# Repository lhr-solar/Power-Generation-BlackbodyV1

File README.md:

# Power Generation Blackbody
Gathers irradiance and temperature data for telemetry and MPPT algorithmic input.

**Blackbody**

Gathers irradiance reading from sensor board and temperature reading from thermocouple. Sends data on telemetry CAN bus.

**Irradiance Sensor Board**

Holds the irradiance sensor. Placed on the top shell between solar modules and connected with wires to blackbody

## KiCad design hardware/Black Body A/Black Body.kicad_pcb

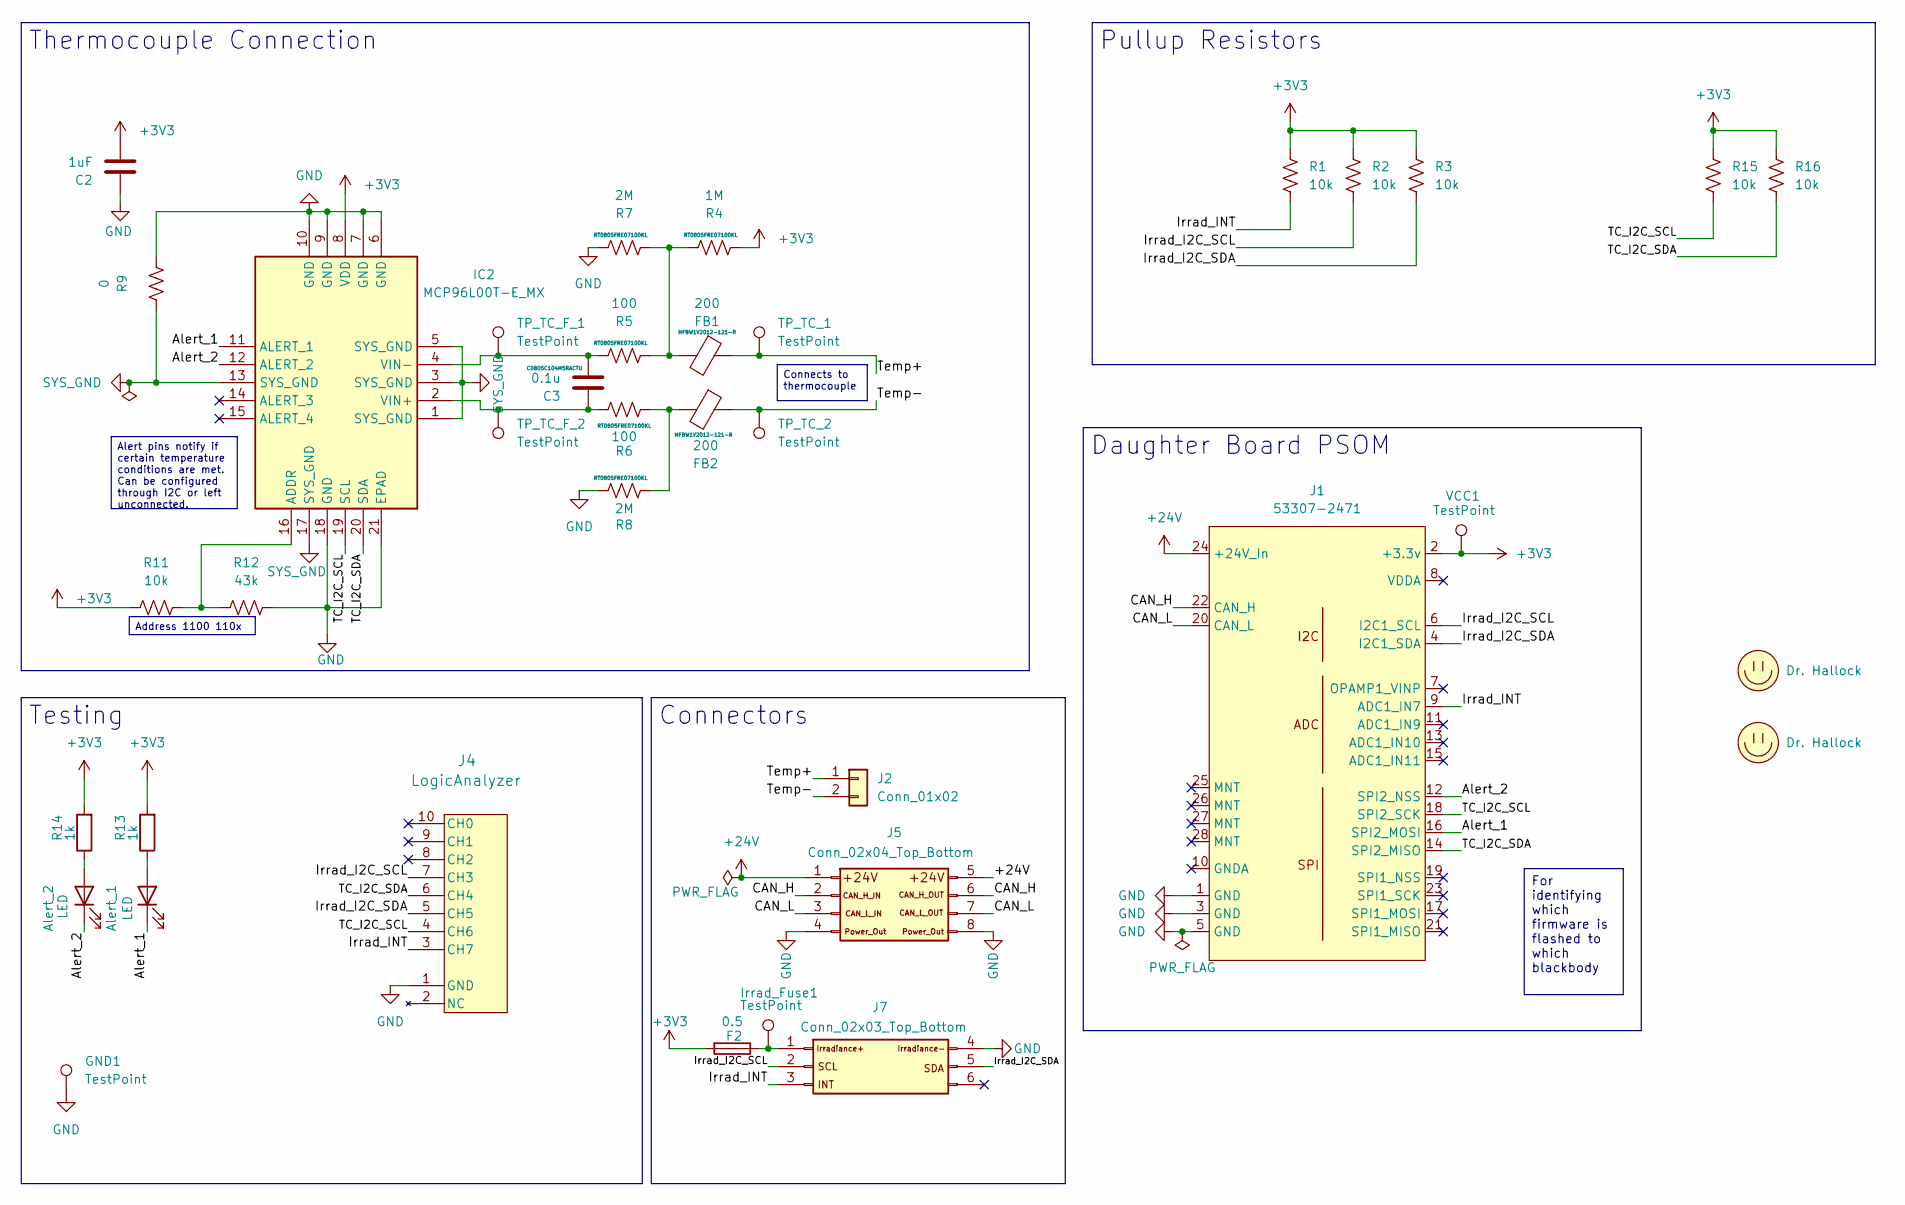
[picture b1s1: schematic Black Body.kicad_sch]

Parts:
Alert_1, Alert_2: LED; LED_0603_1608Metric_Pad1.05x0.95mm_HandSolder
C2: 1uF; C_0805_2012Metric_Pad1.18x1.45mm_HandSolder
C3: 0.1u; C_0805_2012Metric_Pad1.18x1.45mm_HandSolder
F2: 0.5; Fuseholder_Blade_Mini_Keystone_3568
FB1, FB2: 200; L_0603_1608Metric_Pad1.05x0.95mm_HandSolder
GND1: TestPoint; TestPoint_Keystone_5005-5009_Compact
IC2: MCP96L00T-E_MX; QFN65P500X500X100-21N-D; Manufacturer_Part_Number MCP96L00T-E/MX; Mouser Part Number 579-MCP96L00T-E/MX
Irrad_Fuse1: TestPoint; TestPoint_Keystone_5005-5009_Compact
J1: 53307-2471; PeripheralSOM
J2: Conn_01x02; 105313-2102
J4: LogicAnalyzer; CONN_SFH11-xxxC-D05-ST-XX_SUL; Digikey P/N S9194-ND
J5: Conn_02x04_Top_Bottom; Molex_Nano-Fit_105314-xx08_2x04_P2.50mm_Horizontal
J7: Conn_02x03_Top_Bottom; 105314-1306
LOGO1: Dr. Hallock; LHRs_LOGO
LOGO2: Dr. Hallock; Hallock_Image_Tiny
R1, R2, R3, R11, R15, R16: 10k; R_0603_1608Metric_Pad0.98x0.95mm_HandSolder
R4: 1M; R_0603_1608Metric_Pad0.98x0.95mm_HandSolder
R5, R6: 100; R_0603_1608Metric_Pad0.98x0.95mm_HandSolder
R7, R8: 2M; R_0603_1608Metric_Pad0.98x0.95mm_HandSolder
R9: 0; R_0603_1608Metric_Pad0.98x0.95mm_HandSolder
R12: 43k; R_0603_1608Metric_Pad0.98x0.95mm_HandSolder
R13, R14: 1k; R_0603_1608Metric_Pad0.98x0.95mm_HandSolder
TP_TC_1, TP_TC_2: TestPoint; TestPoint_Keystone_5005-5009_Compact
TP_TC_F_1, TP_TC_F_2: TestPoint; TestPoint_Keystone_5005-5009_Compact
VCC1: TestPoint; TestPoint_Keystone_5005-5009_Compact

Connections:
+3V3: C2.2, F2.2, IC2.8 (VDD), J1.2 (+3.3v), R1.1, R2.1, R3.1, R4.2, R11.2, R13.2, R14.2, R15.1, R16.1, VCC1.1
+24V: J1.24 (+24V_In), J5.1, J5.5
/Alert_1: Alert_1.1 (K), IC2.11 (ALERT_1), J1.16 (SPI2_MOSI)
/Alert_2: Alert_2.1 (K), IC2.12 (ALERT_2), J1.12 (SPI2_NSS)
/CAN_H: J1.22 (CAN_H), J5.2, J5.6
/CAN_L: J1.20 (CAN_L), J5.3, J5.7
/Irrad_I2C_SCL: J1.6 (I2C1_SCL), J4.7 (CH3), J7.2, R2.2
/Irrad_I2C_SDA: J1.4 (I2C1_SDA), J4.5 (CH5), J7.5, R3.2
/Irrad_INT: J1.9 (ADC1_IN7), J4.3 (CH7), J7.3, R1.2
/TC_I2C_SCL: IC2.19 (SCL), J1.18 (SPI2_SCK), J4.4 (CH6), R15.2
/TC_I2C_SDA: IC2.20 (SDA), J1.14 (SPI2_MISO), J4.6 (CH4), R16.2
/Temp+: FB1.1, J2.1, TP_TC_1.1
/Temp-: FB2.1, J2.2, TP_TC_2.1
GND: C2.1, GND1.1, IC2.6 (GND), IC2.7 (GND), IC2.9 (GND), IC2.10 (GND), IC2.18 (GND), IC2.21 (EPAD), J1.1 (GND), J1.3 (GND), J1.5 (GND), J4.1 (GND), J5.4, J5.8, J7.4, R7.1, R8.1, R9.2, R12.1
unnamed: Alert_1.2 (A), R13.1
unnamed: Alert_2.2 (A), R14.1
unnamed: FB1.2, R4.1, R5.2, R7.2
unnamed: FB2.2, R6.2, R8.2
unnamed: IC2.16 (ADDR), R11.1, R12.2
unnamed: C3.1, IC2.2 (VIN+), R6.1, TP_TC_F_2.1
unnamed: C3.2, IC2.4 (VIN-), R5.1, TP_TC_F_1.1
unnamed: F2.1, Irrad_Fuse1.1, J7.1
SYS_GND: IC2.1 (SYS_GND), IC2.3 (SYS_GND), IC2.5 (SYS_GND), IC2.13 (SYS_GND), IC2.17 (SYS_GND), R9.1

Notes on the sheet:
Connects to thermocouple
Daughter Board PSOM
Pullup Resistors
Address 1100 110x
For identifying which firmware is flashed to which blackbody
Thermocouple Connection
Testing
Alert pins notify if certain temperature conditions are met. Can be configured through I2C or left unconnected.
Connectors

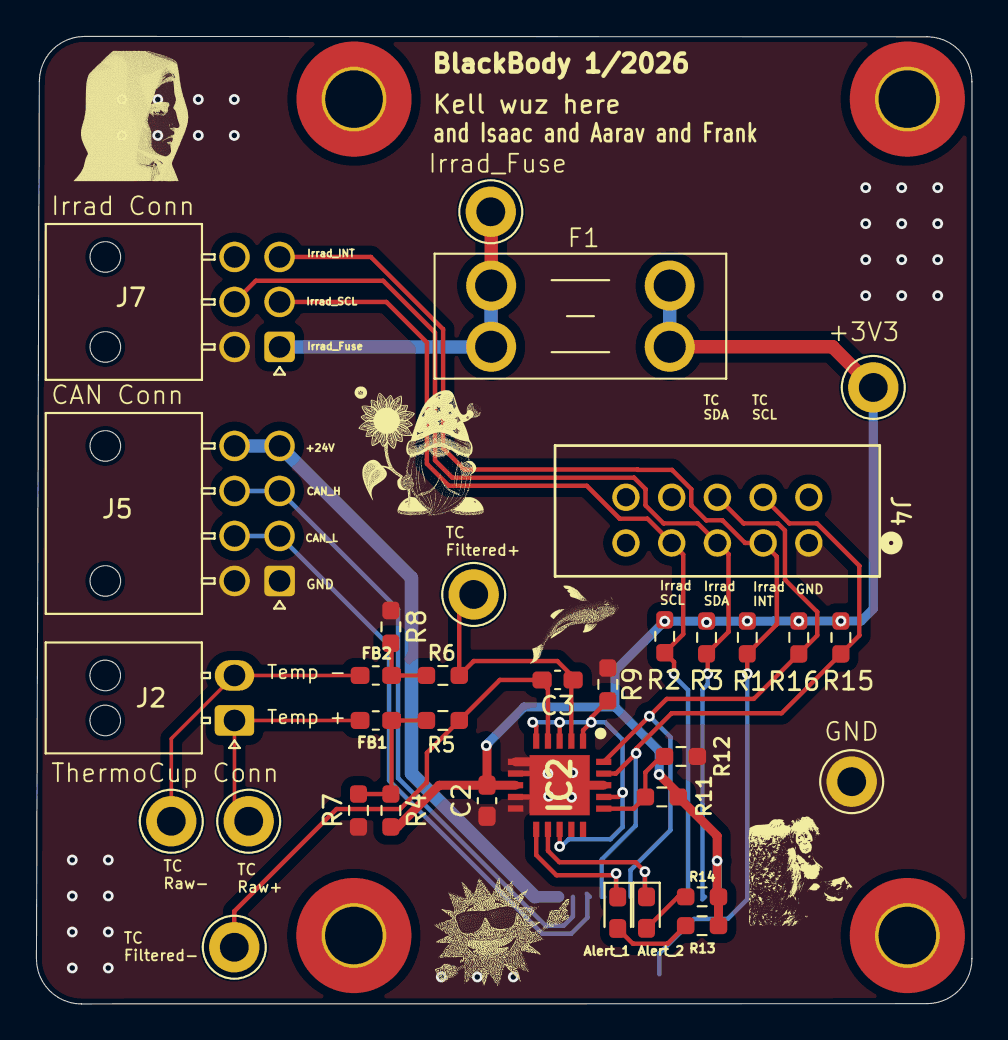
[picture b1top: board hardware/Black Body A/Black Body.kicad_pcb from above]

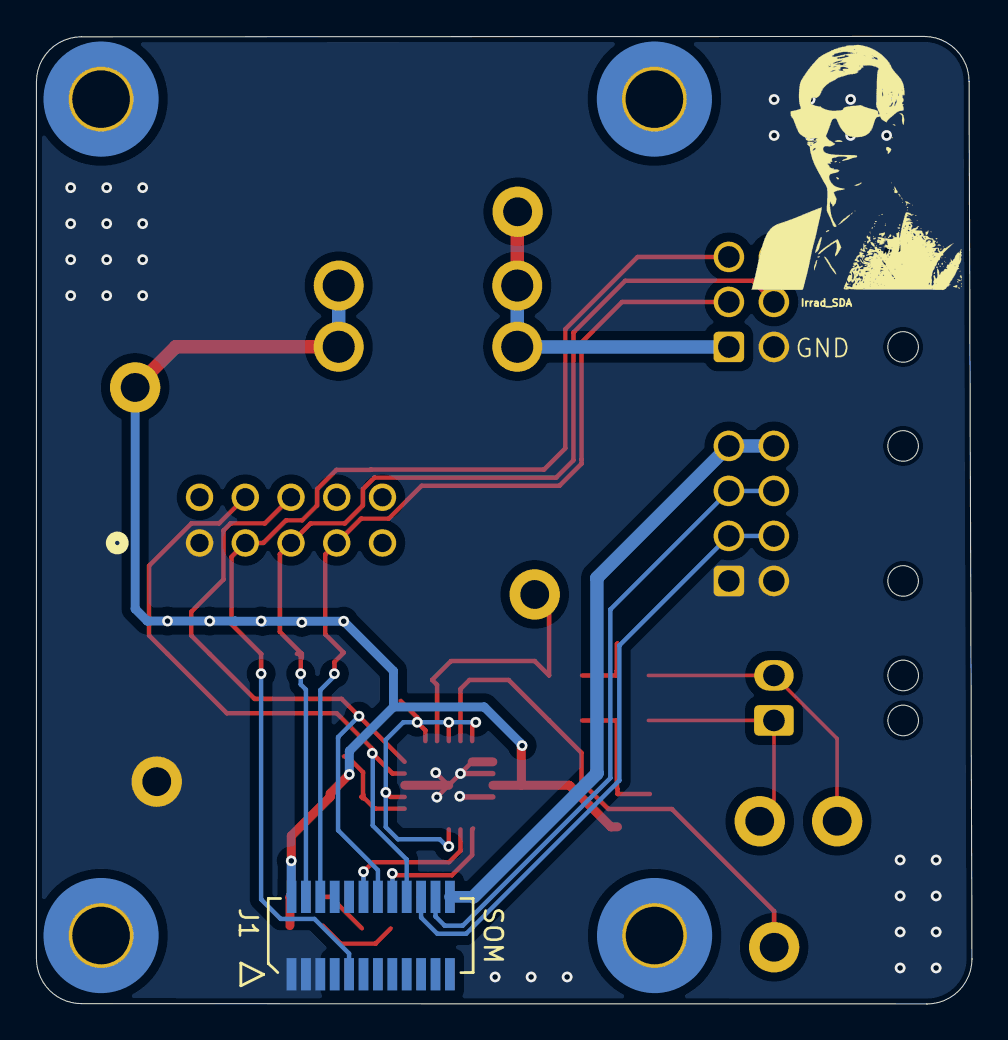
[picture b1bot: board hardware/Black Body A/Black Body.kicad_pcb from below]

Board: 2 copper layers, 52.0 x 53.8 mm, 37 parts (2 on the bottom side), 23 nets.

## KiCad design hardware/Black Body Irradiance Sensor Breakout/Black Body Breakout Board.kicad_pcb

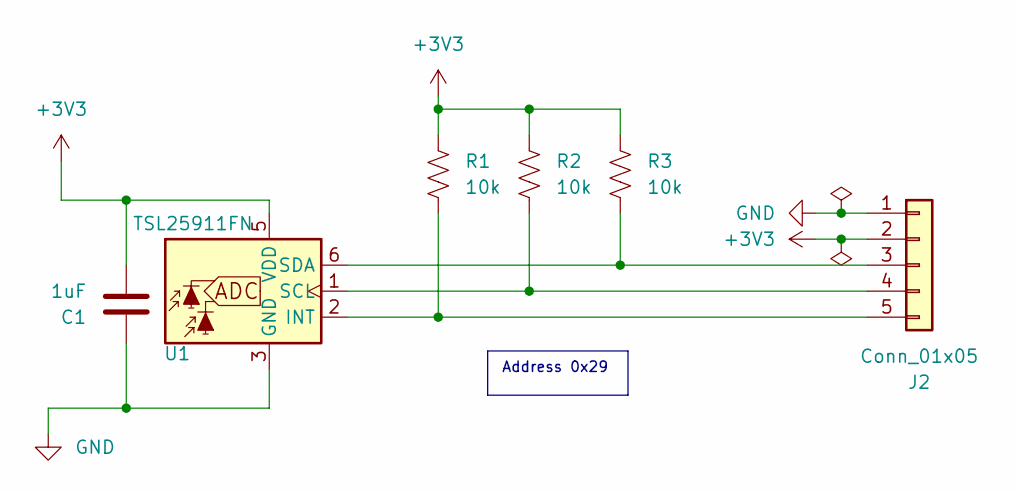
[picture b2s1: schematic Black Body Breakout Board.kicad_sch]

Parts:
C1: 1uF; C_0201_0603Metric_Pad0.64x0.40mm_HandSolder
J2: Conn_01x05; Molex_Nano-Fit_105313-xx05_1x05_P2.50mm_Horizontal
R1, R2, R3: 10k; R_0805_2012Metric
U1: TSL25911FN; AMS_TSL25911FN

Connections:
+3V3: C1.2, J2.2, R1.1, R2.1, R3.1, U1.5 (VDD)
GND: C1.1, J2.1, U1.3 (GND)
unnamed: J2.3, R3.2, U1.6 (SDA)
unnamed: J2.4, R2.2, U1.1 (SCL)
unnamed: J2.5, R1.2, U1.2 (INT)

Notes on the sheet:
Address 0x29

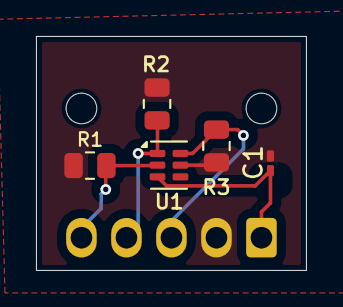
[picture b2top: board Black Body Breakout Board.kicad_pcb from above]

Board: 2 copper layers, 15.0 x 13.0 mm, 6 parts (1 on the bottom side), 5 nets.

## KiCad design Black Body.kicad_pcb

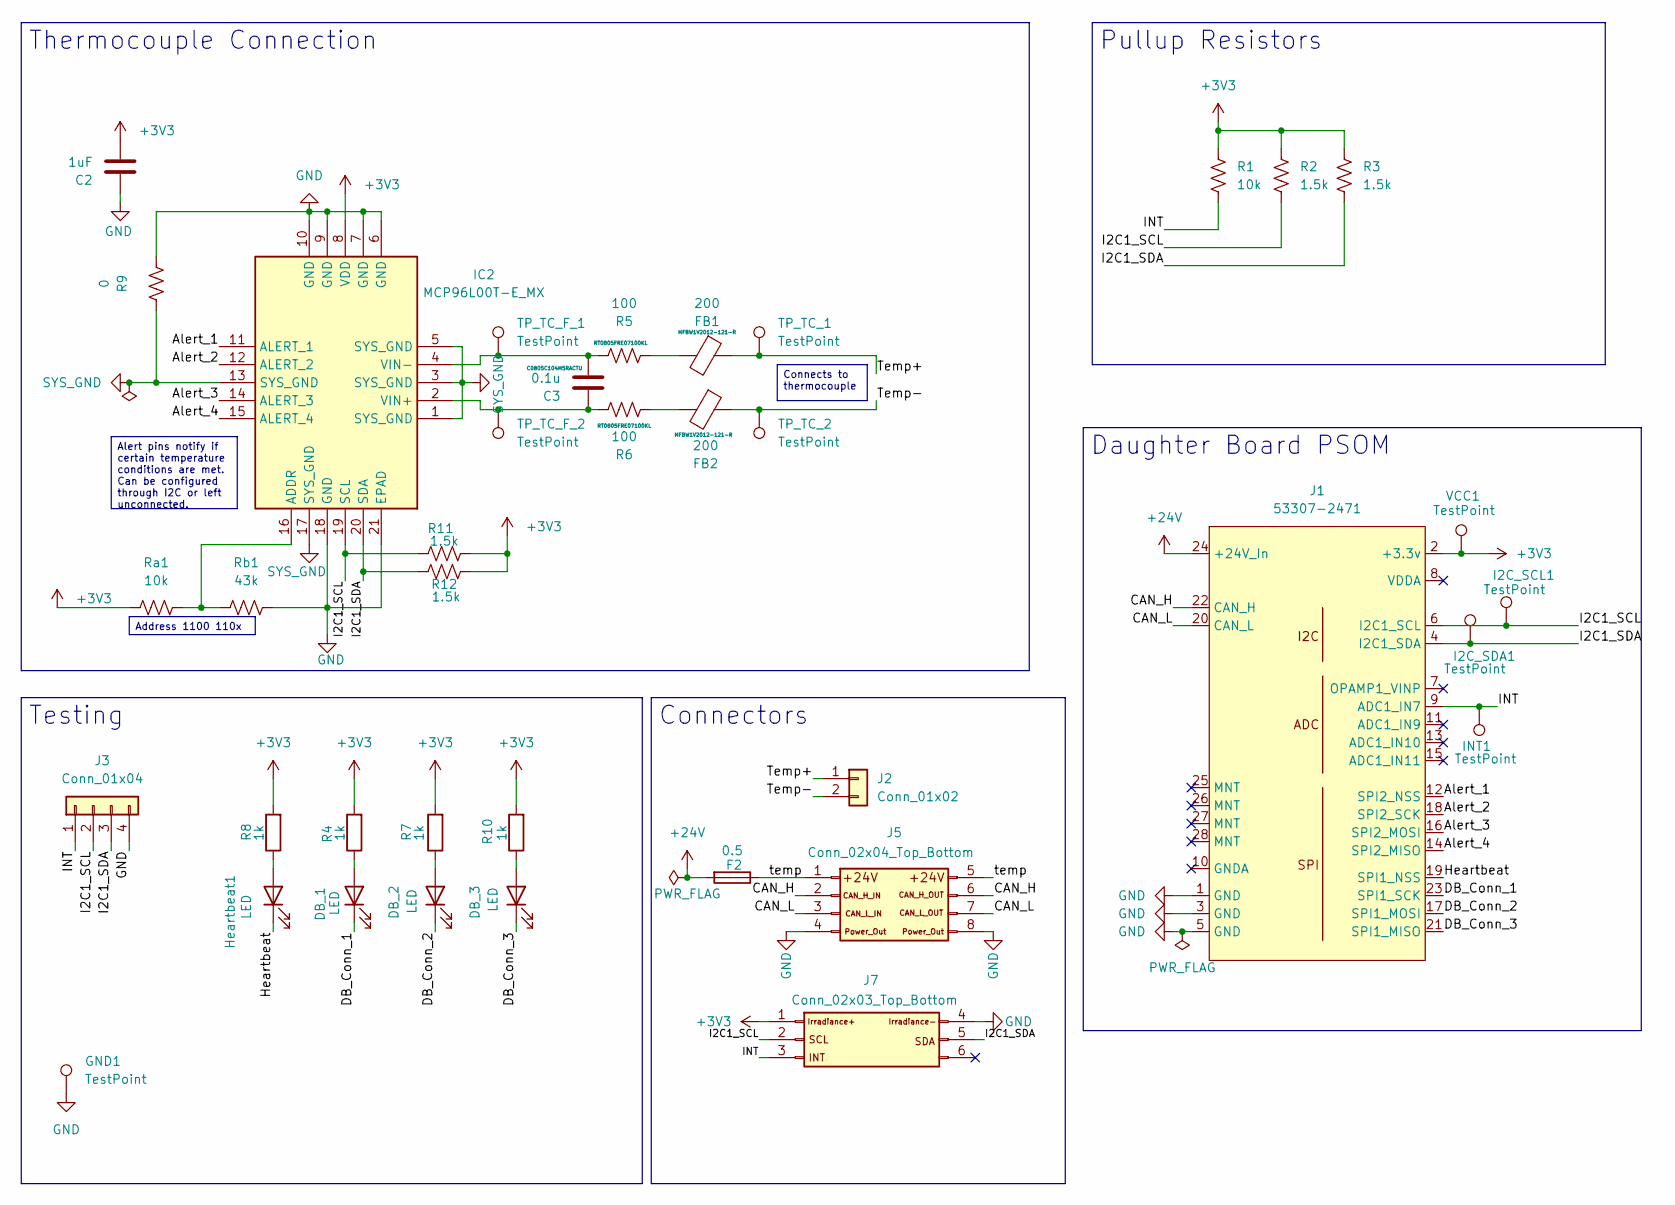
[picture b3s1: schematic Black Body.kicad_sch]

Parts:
C2: 1uF; C_0805_2012Metric_Pad1.18x1.45mm_HandSolder
C3: 0.1u; C_0805_2012Metric_Pad1.18x1.45mm_HandSolder
DB_1, DB_2, DB_3: LED; LED_0603_1608Metric_Pad1.05x0.95mm_HandSolder
F2: 0.5; Fuseholder_Blade_Mini_Keystone_3568
FB1, FB2: 200; L_0603_1608Metric_Pad1.05x0.95mm_HandSolder
GND1: TestPoint; TestPoint_Pad_1.0x1.0mm
Heartbeat1: LED; LED_0603_1608Metric_Pad1.05x0.95mm_HandSolder
I2C_SCL1, I2C_SDA1: TestPoint; PinHeader_1x01_P2.54mm_Vertical
IC2: MCP96L00T-E_MX; QFN65P500X500X100-21N-D; Manufacturer_Part_Number MCP96L00T-E/MX; Mouser Part Number 579-MCP96L00T-E/MX
INT1: TestPoint; PinHeader_1x01_P2.54mm_Vertical
J1: 53307-2471; PeripheralSOM
J2: Conn_01x02; Molex_Nano-Fit_105313-xx02_1x02_P2.50mm_Horizontal
J3: Conn_01x04; Molex_Nano-Fit_105313-xx04_1x04_P2.50mm_Horizontal
J5: Conn_02x04_Top_Bottom; Molex_Nano-Fit_105314-xx08_2x04_P2.50mm_Horizontal
J7: Conn_02x03_Top_Bottom; Molex_Nano-Fit_105314-xx06_2x03_P2.50mm_Horizontal
R1: 10k; R_0805_2012Metric
R2, R3, R11, R12: 1.5k; R_0805_2012Metric
R4, R7, R8, R10: 1k; R_0603_1608Metric_Pad0.98x0.95mm_HandSolder
R5, R6: 100; R_0603_1608Metric_Pad0.98x0.95mm_HandSolder
R9: 0; R_0603_1608Metric_Pad0.98x0.95mm_HandSolder
Ra1: 10k; R_0603_1608Metric_Pad0.98x0.95mm_HandSolder
Rb1: 43k; R_0603_1608Metric_Pad0.98x0.95mm_HandSolder
TP_TC_1, TP_TC_2: TestPoint; TestPoint_Pad_1.0x1.0mm
TP_TC_F_1, TP_TC_F_2: TestPoint; TestPoint_Pad_1.0x1.0mm
VCC1: TestPoint; TestPoint_Pad_1.0x1.0mm

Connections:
+3V3: C2.2, IC2.8 (VDD), J1.2 (+3.3v), J7.1, R1.1, R2.1, R3.1, R4.2, R7.2, R8.2, R10.2, R11.2, R12.2, Ra1.2, VCC1.1
+24V: F2.2, J1.24 (+24V_In)
/Alert_1: IC2.11 (ALERT_1), J1.12 (SPI2_NSS)
/Alert_2: IC2.12 (ALERT_2), J1.18 (SPI2_SCK)
/Alert_3: IC2.14 (ALERT_3), J1.16 (SPI2_MOSI)
/Alert_4: IC2.15 (ALERT_4), J1.14 (SPI2_MISO)
/CAN_H: J1.22 (CAN_H), J5.2, J5.6
/CAN_L: J1.20 (CAN_L), J5.3, J5.7
/DB_Conn_1: DB_1.1 (K), J1.23 (SPI1_SCK)
/DB_Conn_2: DB_2.1 (K), J1.17 (SPI1_MOSI)
/DB_Conn_3: DB_3.1 (K), J1.21 (SPI1_MISO)
/Heartbeat: Heartbeat1.1 (K), J1.19 (SPI1_NSS)
/I2C1_SCL: I2C_SCL1.1, IC2.19 (SCL), J1.6 (I2C1_SCL), J3.2, J7.2, R2.2, R11.1
/I2C1_SDA: I2C_SDA1.1, IC2.20 (SDA), J1.4 (I2C1_SDA), J3.3, J7.5, R3.2, R12.1
/INT: INT1.1, J1.9 (ADC1_IN7), J3.1, J7.3, R1.2
/Temp+: FB1.1, J2.1, TP_TC_1.1
/Temp-: FB2.1, J2.2, TP_TC_2.1
/temp: F2.1, J5.1, J5.5
GND: C2.1, GND1.1, IC2.6 (GND), IC2.7 (GND), IC2.9 (GND), IC2.10 (GND), IC2.18 (GND), IC2.21 (EPAD), J1.1 (GND), J1.3 (GND), J1.5 (GND), J3.4, J5.4, J5.8, J7.4, R9.2, Rb1.1
unnamed: DB_1.2 (A), R4.1
unnamed: DB_2.2 (A), R7.1
unnamed: DB_3.2 (A), R10.1
unnamed: FB1.2, R5.2
unnamed: FB2.2, R6.2
unnamed: Heartbeat1.2 (A), R8.1
unnamed: IC2.16 (ADDR), Ra1.1, Rb1.2
unnamed: C3.1, IC2.2 (VIN+), R6.1, TP_TC_F_2.1
unnamed: C3.2, IC2.4 (VIN-), R5.1, TP_TC_F_1.1
SYS_GND: IC2.1 (SYS_GND), IC2.3 (SYS_GND), IC2.5 (SYS_GND), IC2.13 (SYS_GND), IC2.17 (SYS_GND), R9.1

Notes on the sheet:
Connects to thermocouple
Daughter Board PSOM
Pullup Resistors
Address 1100 110x
Thermocouple Connection
Testing
Alert pins notify if certain temperature conditions are met. Can be configured through I2C or left unconnected.
Connectors

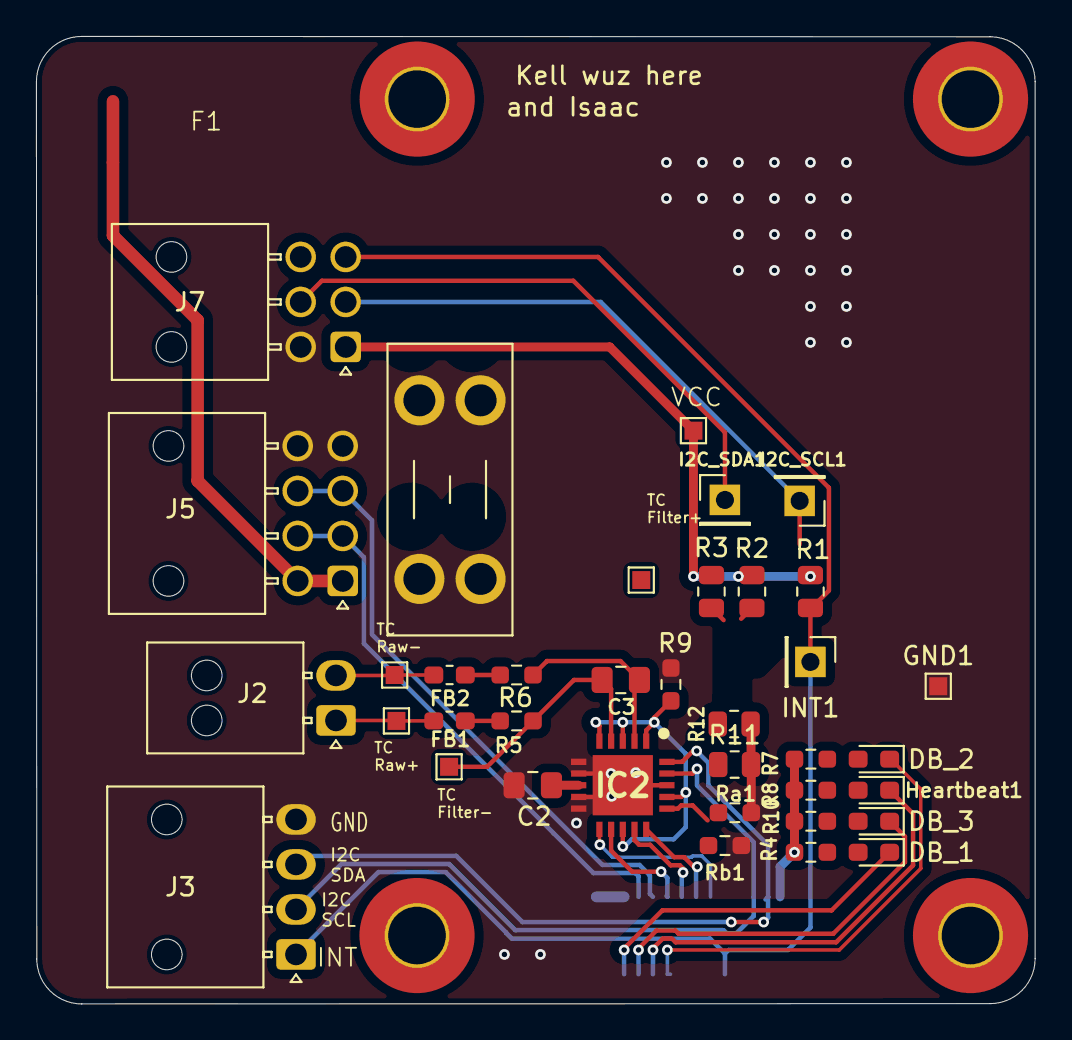
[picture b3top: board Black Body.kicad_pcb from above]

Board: 2 copper layers, 55.5 x 53.8 mm, 38 parts (1 on the bottom side), 29 nets.

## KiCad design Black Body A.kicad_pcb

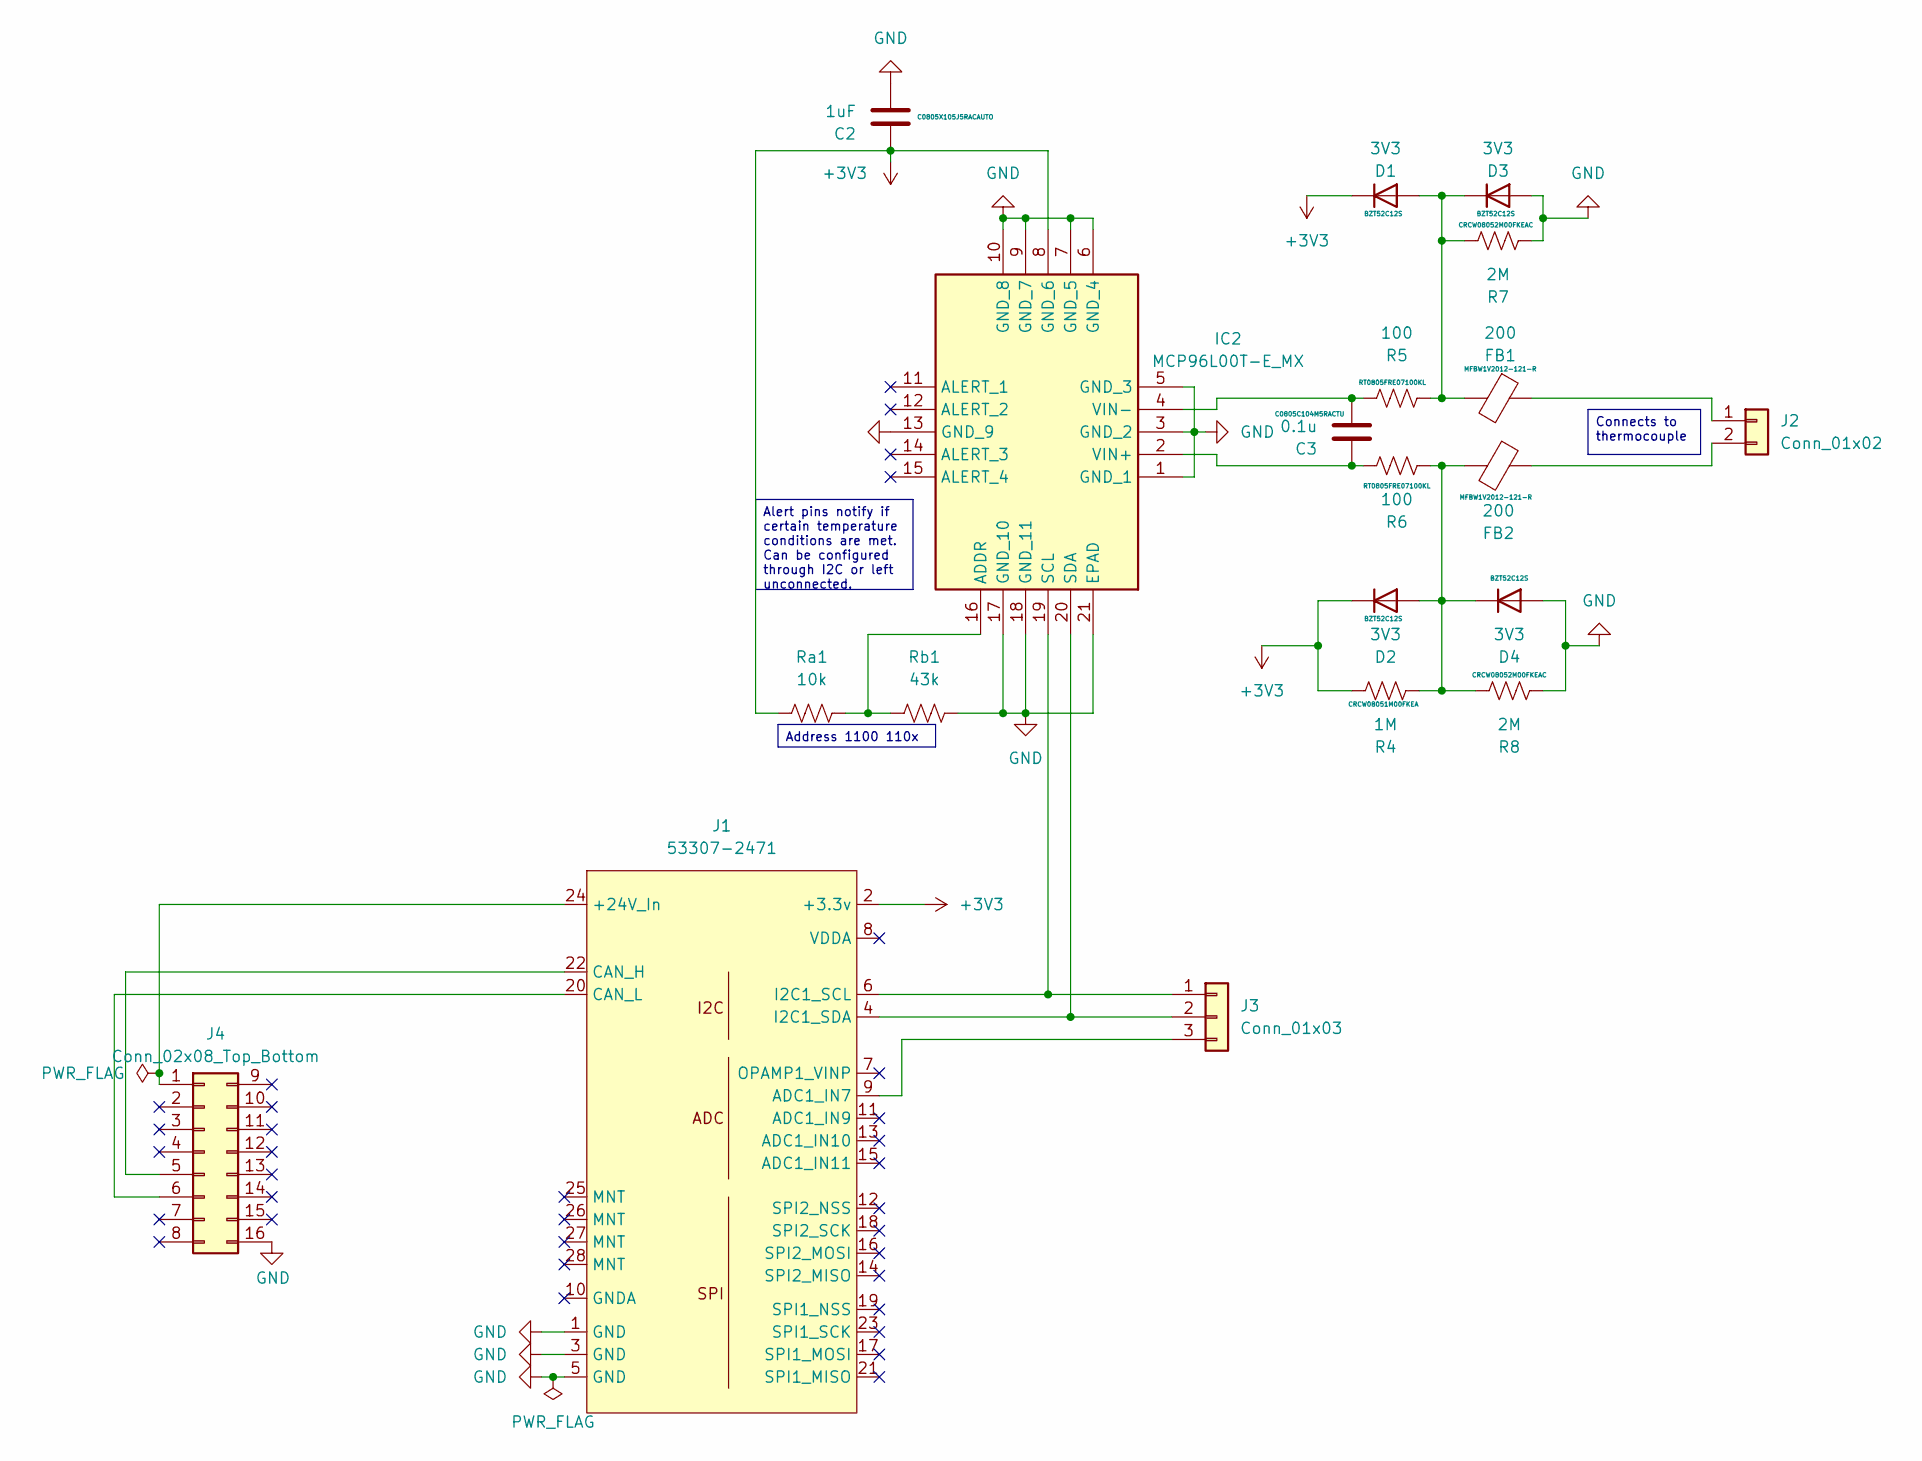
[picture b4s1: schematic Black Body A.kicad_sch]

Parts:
C2: 1uF; C_0805_2012Metric_Pad1.18x1.45mm_HandSolder
C3: 0.1u; C_0805_2012Metric_Pad1.18x1.45mm_HandSolder
D1, D2, D3, D4: 3V3; D_0603_1608Metric_Pad1.05x0.95mm_HandSolder
FB1, FB2: 200; L_0603_1608Metric_Pad1.05x0.95mm_HandSolder
IC2: MCP96L00T-E_MX; QFN65P500X500X100-21N-D; Manufacturer_Part_Number MCP96L00T-E/MX; Mouser Part Number 579-MCP96L00T-E/MX
J1: 53307-2471; PeripheralSOM
J2: Conn_01x02; Molex_Nano-Fit_105313-xx02_1x02_P2.50mm_Horizontal
J3: Conn_01x03; Molex_Nano-Fit_105313-xx03_1x03_P2.50mm_Horizontal
J4: Conn_02x08_Top_Bottom; CONN_SD-75900-001_2X08_MOL
R4: 1M; R_0603_1608Metric_Pad0.98x0.95mm_HandSolder
R5, R6: 100; R_0603_1608Metric_Pad0.98x0.95mm_HandSolder
R7, R8: 2M; R_0603_1608Metric_Pad0.98x0.95mm_HandSolder
Ra1: 10k; R_0603_1608Metric_Pad0.98x0.95mm_HandSolder
Rb1: 43k; R_0603_1608Metric_Pad0.98x0.95mm_HandSolder

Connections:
+3V3: C2.1, D1.1 (K), D2.1 (K), IC2.8 (GND_6), J1.2 (+3.3v), R4.2, Ra1.2
GND: C2.2, D3.2 (A), D4.2 (A), IC2.1 (GND_1), IC2.3 (GND_2), IC2.5 (GND_3), IC2.6 (GND_4), IC2.7 (GND_5), IC2.9 (GND_7), IC2.10 (GND_8), IC2.13 (GND_9), IC2.17 (GND_10), IC2.18 (GND_11), IC2.21 (EPAD), J1.1 (GND), J1.3 (GND), J1.5 (GND), J4.16, R7.1, R8.1, Rb1.1
unnamed: D1.2 (A), D3.1 (K), FB1.2, R5.2, R7.2
unnamed: D2.2 (A), D4.1 (K), FB2.2, R4.1, R6.2, R8.2
unnamed: IC2.16 (ADDR), Ra1.1, Rb1.2
unnamed: IC2.19 (SCL), J1.6 (I2C1_SCL), J3.1
unnamed: IC2.20 (SDA), J1.4 (I2C1_SDA), J3.2
unnamed: C3.1, IC2.2 (VIN+), R6.1
unnamed: C3.2, IC2.4 (VIN-), R5.1
unnamed: J1.24 (+24V_In), J4.1
unnamed: J1.9 (ADC1_IN7), J3.3
unnamed: J1.22 (CAN_H), J4.5
unnamed: J1.20 (CAN_L), J4.6
unnamed: FB1.1, J2.1
unnamed: FB2.1, J2.2

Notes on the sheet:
Connects to thermocouple
Address 1100 110x
Alert pins notify if certain temperature conditions are met. Can be configured through I2C or left unconnected.

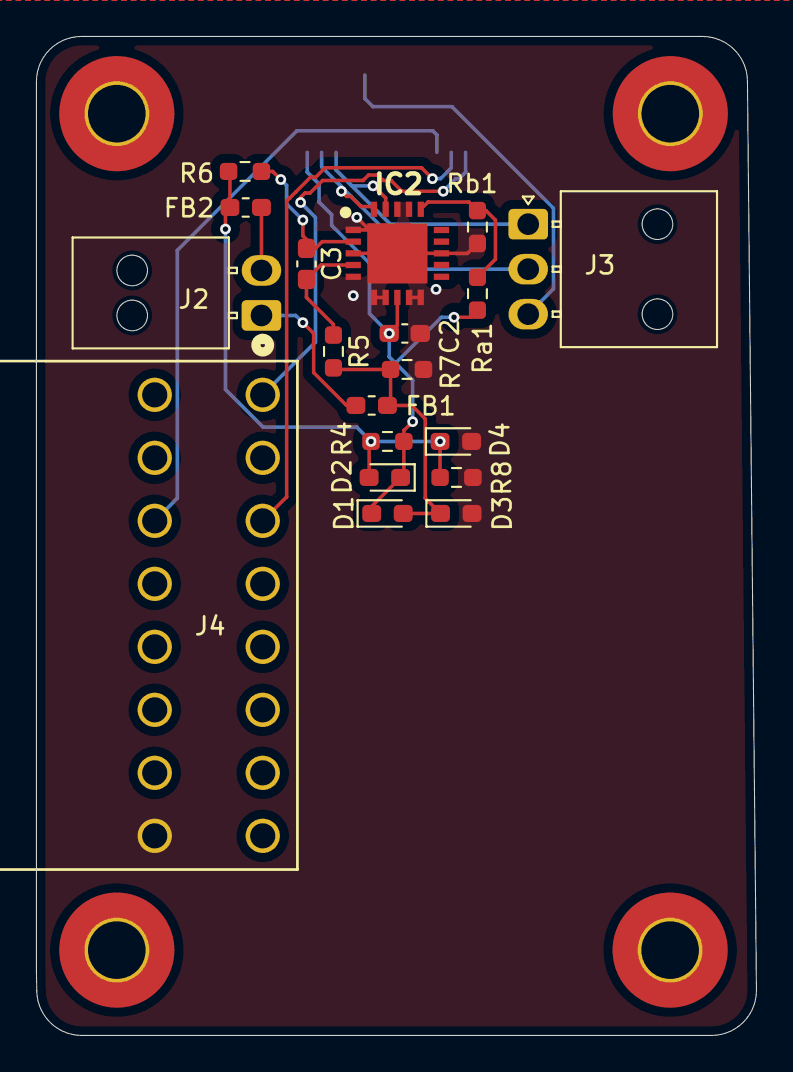
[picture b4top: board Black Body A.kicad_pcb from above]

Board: 2 copper layers, 40.0 x 55.5 mm, 20 parts (1 on the bottom side), 15 nets.

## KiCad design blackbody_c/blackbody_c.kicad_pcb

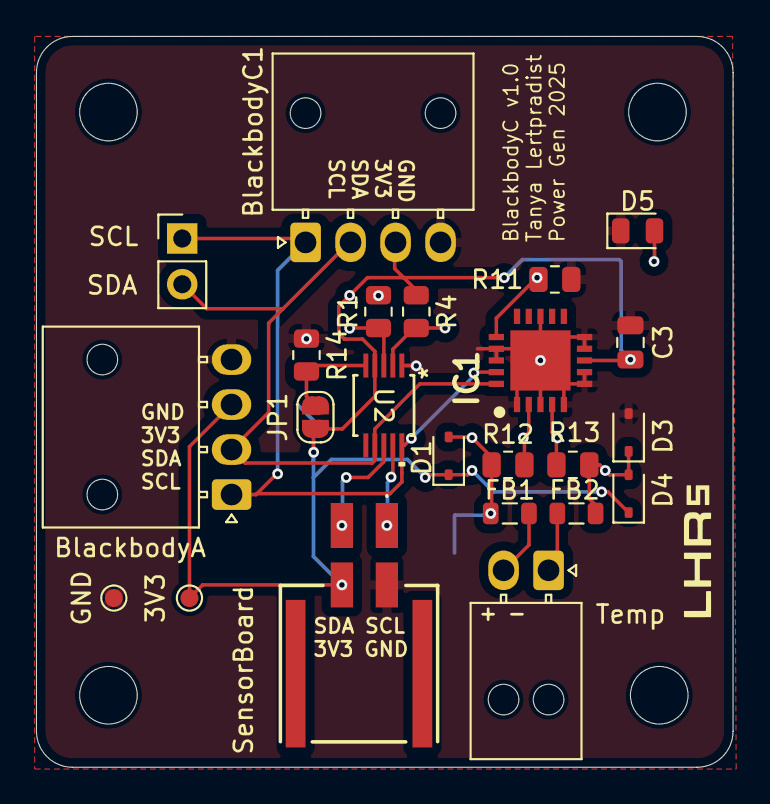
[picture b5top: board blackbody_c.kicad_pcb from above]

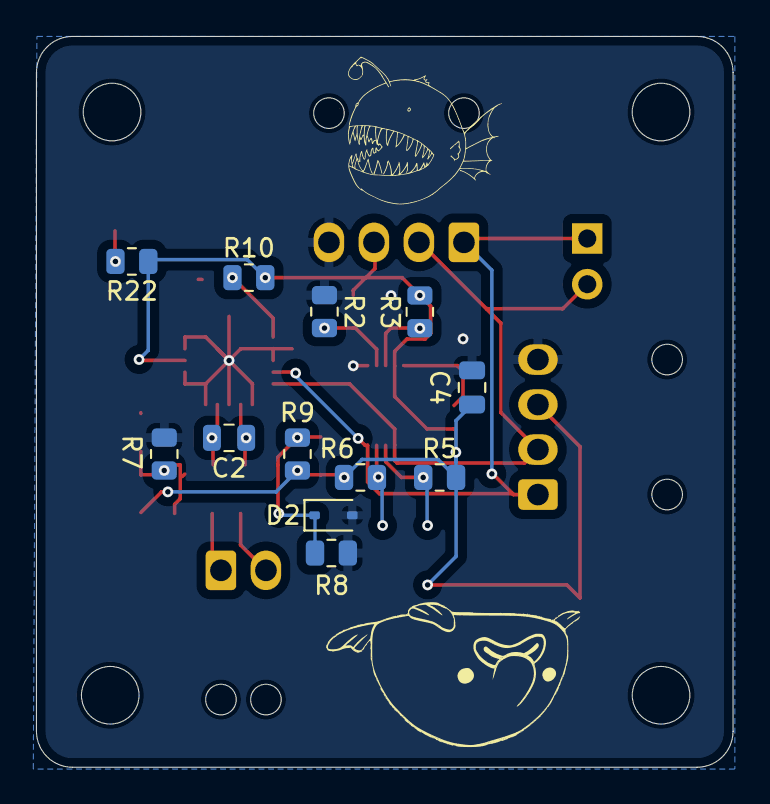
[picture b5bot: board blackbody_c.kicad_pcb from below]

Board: 2 copper layers, 38.7 x 40.6 mm, 39 parts (12 on the bottom side), 17 nets.

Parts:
3V3: TestPoint; TestPoint_Pad_D1.0mm
BlackbodyA: Conn_01x04; Molex_Nano-Fit_105313-xx04_1x04_P2.50mm_Horizontal
BlackbodyC1: Conn_01x04; Molex_Nano-Fit_105313-xx04_1x04_P2.50mm_Horizontal
C2: 0.1u; C_0805_2012Metric
C3: 1uF; C_0805_2012Metric
C4: 10uF; C_0805_2012Metric
D1, D2, D3, D4: D; D_SOD-323
D5: Power; LED_0805_2012Metric
FB1, FB2: FerriteBead; L_0805_2012Metric
GND: TestPoint; TestPoint_Pad_D1.0mm
H1, H2, H3, H4: MountingHole; MountingHole_3.2mm_M3
IC1: MCP96L00T-E_MX; QFN65P500X500X100-21N-D
J1: Conn_01x02; PinHeader_1x02_P2.54mm_Vertical
JP1: SolderJumper_2_Open; SolderJumper-2_P1.3mm_Open_RoundedPad1.0x1.5mm
R1: R_LB; R_0805_2012Metric
R2: R_HB; R_0805_2012Metric
R3: R_LT; R_0805_2012Metric
R4: R_HT; R_0805_2012Metric
R5, R6: 4.7k; R_0805_2012Metric
R7, R8: 2M; R_0805_2012Metric
R9: 1M; R_0805_2012Metric
R10: Ra; R_0805_2012Metric
R11: Rb; R_0805_2012Metric
R12, R13: 100; R_0805_2012Metric
R14: 10k; R_0805_2012Metric
R22: 2.2k; R_0805_2012Metric
SensorBoard: Conn_01x04; 1054051104
Temp: Conn_01x02; Molex_Nano-Fit_105313-xx02_1x02_P2.50mm_Horizontal
U2: LTC4316IMS-PBF; MSOP-10_MS_LIT

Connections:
+3V3: 3V3.1, BlackbodyA.3, BlackbodyC1.3, C3.1, C4.1, D1.1 (K), D4.1 (K), IC1.8 (VDD), JP1.2 (B), R3.2, R4.2, R5.1, R6.1, R9.2, R10.2, R22.1, SensorBoard.4, U2.4 (VCC)
/SCL: BlackbodyA.1, BlackbodyC1.1, IC1.19 (SCL), J1.1, U2.10 (SCLIN)
/SDA: BlackbodyA.2, BlackbodyC1.2, IC1.20 (SDA), J1.2, U2.7 (SDAIN)
/irradiance/SCL_board: R6.2, SensorBoard.1, U2.9 (SCLOUT)
/irradiance/SDA_board: R5.2, SensorBoard.2, U2.8 (SDAOUT)
GND: BlackbodyA.4, BlackbodyC1.4, C3.2, C4.2, D2.2 (A), D3.2 (A), D5.1 (K), GND.1, IC1.1 (GND_1), IC1.3 (GND_2), IC1.5 (GND_3), IC1.6 (GND_4), IC1.7 (GND_5), IC1.9 (GND_7), IC1.10 (GND_8), IC1.13 (GND_9), IC1.17 (GND_10), IC1.18 (GND_11), IC1.21 (EPAD), R1.1, R2.1, R7.1, R8.1, R11.1, R14.1, SensorBoard.3, U2.1 (GND)
unnamed: D1.2 (A), D2.1 (K), FB1.2, R8.2, R9.1, R12.2
unnamed: D3.1 (K), D4.2 (A), FB2.2, R7.2, R13.2
unnamed: D5.2 (A), R22.2
unnamed: IC1.16 (ADDR), R10.1, R11.2
unnamed: C2.1, IC1.2 (VIN+), R12.1
unnamed: C2.2, IC1.4 (VIN-), R13.1
unnamed: FB1.1, Temp.2 (Pin_1)
unnamed: FB2.1, Temp.1 (Pin_2)
unnamed: JP1.1 (A), R14.2, U2.5 (ENABLE)
unnamed: R2.2, R4.1, U2.2 (XORH)
unnamed: R1.2, R3.1, U2.3 (XORL)
